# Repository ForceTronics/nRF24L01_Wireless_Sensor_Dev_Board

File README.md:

# nRF24L01_Wireless_Sensor_Dev_Board
This repository is for Arduino code that goes to an open source Wireless Sensor Development Board that is being developed on the ForceTronics YouTube channel. Please note that this code is still currently in early draft form. The Wireless Sensor Dev Board will feature an ATmega 328p MCU and a nRF24L01+ Transceiver Module. The 328p will be programmed using the Arduino IDE (Pro Mini 3.3V 8MHz bootloader). In the future this wireless sensor dev board will be available for sale at www.forcetronics.com

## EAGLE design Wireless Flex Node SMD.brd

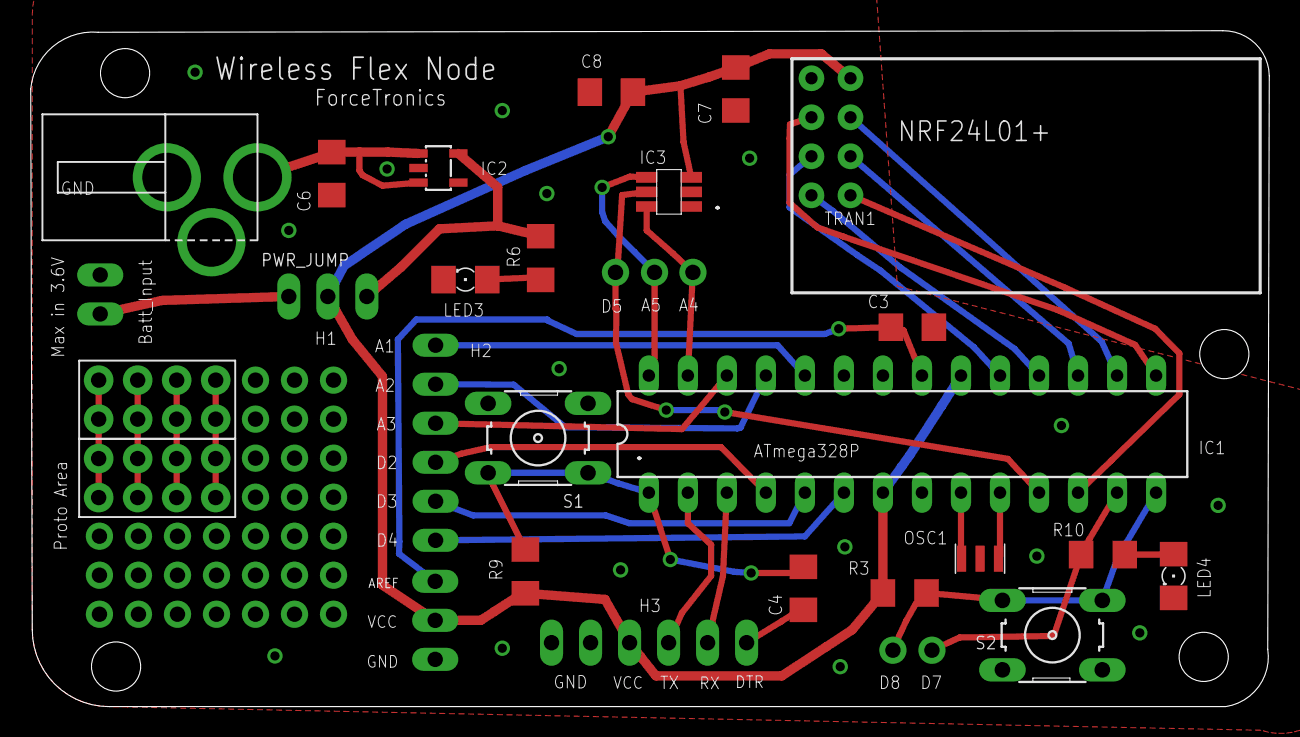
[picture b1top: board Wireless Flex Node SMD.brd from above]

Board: 2 copper layers, 80.6 x 44.0 mm, 31 parts (0 on the bottom side), 35 nets.

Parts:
A4, A5: 1PINHEADER_S
BATT_INPUT: 2PINHEADER
C3, C4, C8: 0.1uF; C1206
C6, C7: 10uF; C1206
D5, D7, D8: 1PINHEADER_S
DGHDFGH: ATMEGA168-PU; DIL28-3
IC2: LP2985; SOT23
LED3, LED4: 1206
N1, N5: 6PINHEADER
N3: 2.1MM_DC_JACK
NRF24L01+: NRF24L01A; NRF24L01
OSC1: CSTCE_RESONATOR
P1, P2: 2X4_HEADER
PWR_JUMP: 3PINHEADER
R3: 100k; R1206
R6, R10: 220; R1206
R9: 10k; R1206
S1, S2: B3F-10XX
U$2: 3PINHEADER
U$8: STTS751; STTS751-SOT23-6L

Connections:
A5: D5.P$1, DGHDFGH.11, U$8.5
GND: BATT_INPUT.P0, C3.2, C6.2, C7.2, C8.2, DGHDFGH.8, DGHDFGH.22, IC2.2, LED3.C, LED4.C, N1.P4, N1.P5, N3.GND1, N3.GND2, NRF24L01+.P1, OSC1.2, S1.3, S1.4, S2.3, S2.4, U$2.N0, U$8.1, U$8.2
unnamed: DGHDFGH.10, OSC1.1
unnamed: DGHDFGH.18, NRF24L01+.P7
unnamed: DGHDFGH.19, NRF24L01+.P5
unnamed: DGHDFGH.17, NRF24L01+.P6
unnamed: DGHDFGH.16, NRF24L01+.P4
unnamed: DGHDFGH.15, NRF24L01+.P3
unnamed: D7.P$1, DGHDFGH.13, R10.2
unnamed: C4.2, N1.P0
unnamed: DGHDFGH.9, OSC1.3
unnamed: C4.1, DGHDFGH.1, R9.1, S1.1, S1.2
unnamed: D8.P$1, DGHDFGH.14, R3.1, S2.1, S2.2
unnamed: LED4.A, R10.1
unnamed: DGHDFGH.3, N1.P1
unnamed: DGHDFGH.2, N1.P2
unnamed: C3.1, DGHDFGH.21, U$2.N2
unnamed: DGHDFGH.12, NRF24L01+.P8
unnamed: DGHDFGH.6, N5.P5
unnamed: DGHDFGH.5, N5.P4
unnamed: A5.P$1, DGHDFGH.28, U$8.4
unnamed: A4.P$1, DGHDFGH.27, U$8.6
unnamed: C6.1, IC2.1, IC2.3, N3.VIN
unnamed: IC2.5, PWR_JUMP.N2, R6.2
unnamed: BATT_INPUT.P1, PWR_JUMP.N0
unnamed: LED3.A, R6.1
unnamed: DGHDFGH.4, N5.P3
unnamed: DGHDFGH.26, N5.P2
unnamed: DGHDFGH.25, N5.P1
unnamed: DGHDFGH.24, N5.P0
unnamed: P1.P1, P1.P5, P2.P1, P2.P5
unnamed: P1.P2, P1.P6, P2.P2, P2.P6
unnamed: P1.P3, P1.P7, P2.P3, P2.P7
unnamed: P1.P4, P1.P8, P2.P4, P2.P8
VCC: C7.1, C8.1, DGHDFGH.7, DGHDFGH.20, N1.P3, NRF24L01+.P2, PWR_JUMP.N1, R3.2, R9.2, U$2.N1, U$8.3

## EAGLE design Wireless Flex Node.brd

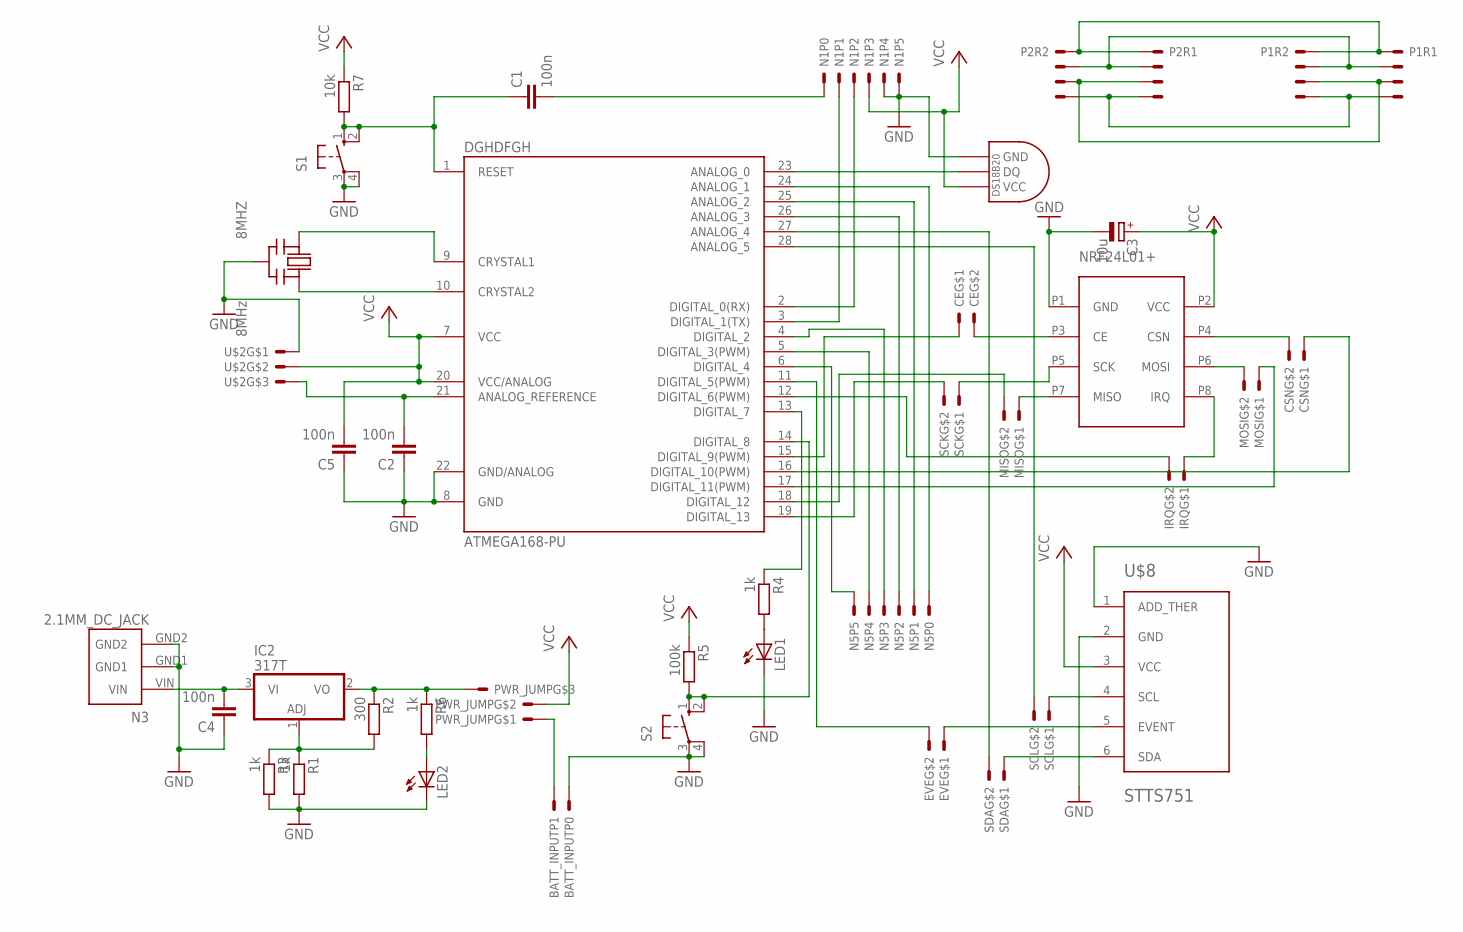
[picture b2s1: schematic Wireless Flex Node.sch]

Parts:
8MHZ: 8MHz; CERM_OSC
BATT_INPUT: 2PINHEADER
C1, C2, C4, C5: 100n; C050-030X075
C3: 10u; E2,5-6
CE: 2PINHEADER_S
CSN: 2PINHEADER_S
DGHDFGH: ATMEGA168-PU; DIL28-3
EVE: 2PINHEADER_S
IC2: 317T; TO220H
IRQ: 2PINHEADER_S
LED1, LED2: LED3MM
MISO: 2PINHEADER_S
MOSI: 2PINHEADER_S
N1, N5: 6PINHEADER
N3: 2.1MM_DC_JACK
NRF24L01+: NRF24L01A; NRF24L01
P1, P2: 2X4_HEADER
PWR_JUMP: 3PINHEADER
R1, R3, R4, R6: 1k; 0207/10
R2: 300; 0207/10
R5: 100k; 0207/10
R7: 10k; 0207/10
S1, S2: 10-XX; B3F-10XX
SCK: 2PINHEADER_S
SCL: 2PINHEADER_S
SDA: 2PINHEADER_S
U$2: 3PINHEADER
U$8: STTS751; STTS751-SOT23-6L
U$9: DS1820TO92; DS1820

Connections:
GND: 8MHZ.P$2 (GND), BATT_INPUT.P0, C2.1, C3.-, C4.1, C5.1, DGHDFGH.8 (GND), DGHDFGH.22 (GND/ANALOG), LED1.K (C), LED2.K (C), N1.P4, N1.P5, N3.GND1, N3.GND2, NRF24L01+.P1 (GND), R1.2, R3.2, S1.3, S1.4 (P1), S2.3, S2.4 (P1), U$2.N0, U$8.1 (ADD_THER), U$8.2 (GND), U$9.GND
unnamed: MISO.N0, NRF24L01+.P7 (MISO)
unnamed: DGHDFGH.18 (DIGITAL_12), MISO.N1
unnamed: DGHDFGH.19 (DIGITAL_13), SCK.N1
unnamed: NRF24L01+.P5 (SCK), SCK.N0
unnamed: MOSI.N1, NRF24L01+.P6 (MOSI)
unnamed: DGHDFGH.17 (DIGITAL_11(PWM)), MOSI.N0
unnamed: CE.N1, NRF24L01+.P3 (CE)
unnamed: CSN.N0, DGHDFGH.16 (DIGITAL_10(PWM))
unnamed: CSN.N1, NRF24L01+.P4 (CSN)
unnamed: CE.N0, DGHDFGH.15 (DIGITAL_9(PWM))
unnamed: DGHDFGH.13 (DIGITAL_7), R4.1
unnamed: C1.2, N1.P0
unnamed: 8MHZ.P$1 (IN), DGHDFGH.9 (CRYSTAL1)
unnamed: 8MHZ.P$3 (OUT), DGHDFGH.10 (CRYSTAL2)
unnamed: C1.1, DGHDFGH.1 (RESET), R7.2, S1.1 (S), S1.2 (S1)
unnamed: DGHDFGH.14 (DIGITAL_8), R5.2, S2.1 (S), S2.2 (S1)
unnamed: LED1.A, R4.2
unnamed: IRQ.N0, NRF24L01+.P8 (IRQ)
unnamed: DGHDFGH.3 (DIGITAL_1(TX)), N1.P1
unnamed: DGHDFGH.2 (DIGITAL_0(RX)), N1.P2
unnamed: C2.2, DGHDFGH.21 (ANALOG_REFERENCE), U$2.N2
unnamed: DGHDFGH.12 (DIGITAL_6(PWM)), IRQ.N1
unnamed: DGHDFGH.6 (DIGITAL_4), N5.P5
unnamed 26: DGHDFGH.23 (ANALOG_0), U$9.DQ; also elsewhere on the board
unnamed: DGHDFGH.5 (DIGITAL_3(PWM)), N5.P4
unnamed: SCL.N0, U$8.4 (SCL)
unnamed: DGHDFGH.28 (ANALOG_5), SCL.N1
unnamed: SDA.N0, U$8.6 (SDA)
unnamed: DGHDFGH.27 (ANALOG_4), SDA.N1
unnamed: EVE.N0, U$8.5 (EVENT)
unnamed: DGHDFGH.11 (DIGITAL_5(PWM)), EVE.N1
unnamed 34: C4.2, IC2.3 (VI), N3.VIN; also elsewhere on the board
unnamed 35: IC2.1 (ADJ), R1.1, R2.2, R3.1; also elsewhere on the board
unnamed 36: IC2.2 (VO), PWR_JUMP.N2, R2.1, R6.1; also elsewhere on the board
unnamed: BATT_INPUT.P1, PWR_JUMP.N0
unnamed: LED2.A, R6.2
unnamed: DGHDFGH.4 (DIGITAL_2), N5.P3
unnamed: DGHDFGH.26 (ANALOG_3), N5.P2
unnamed: DGHDFGH.25 (ANALOG_2), N5.P1
unnamed: DGHDFGH.24 (ANALOG_1), N5.P0
unnamed: P1.P1 (S), P1.P5 (S), P2.P1 (S), P2.P5 (S)
unnamed: P1.P2 (S1), P1.P6 (S1), P2.P2 (S1), P2.P6 (S1)
unnamed: P1.P3 (S2), P1.P7 (S2), P2.P3 (S2), P2.P7 (S2)
unnamed: P1.P4 (S3), P1.P8 (S3), P2.P4 (S3), P2.P8 (S3)
VCC: C3.+, C5.2, DGHDFGH.7 (VCC), DGHDFGH.20 (VCC/ANALOG), N1.P3, NRF24L01+.P2 (VCC), PWR_JUMP.N1, R5.1, R7.1, U$2.N1, U$8.3 (VCC), U$9.VDD (VCC); also elsewhere on the board

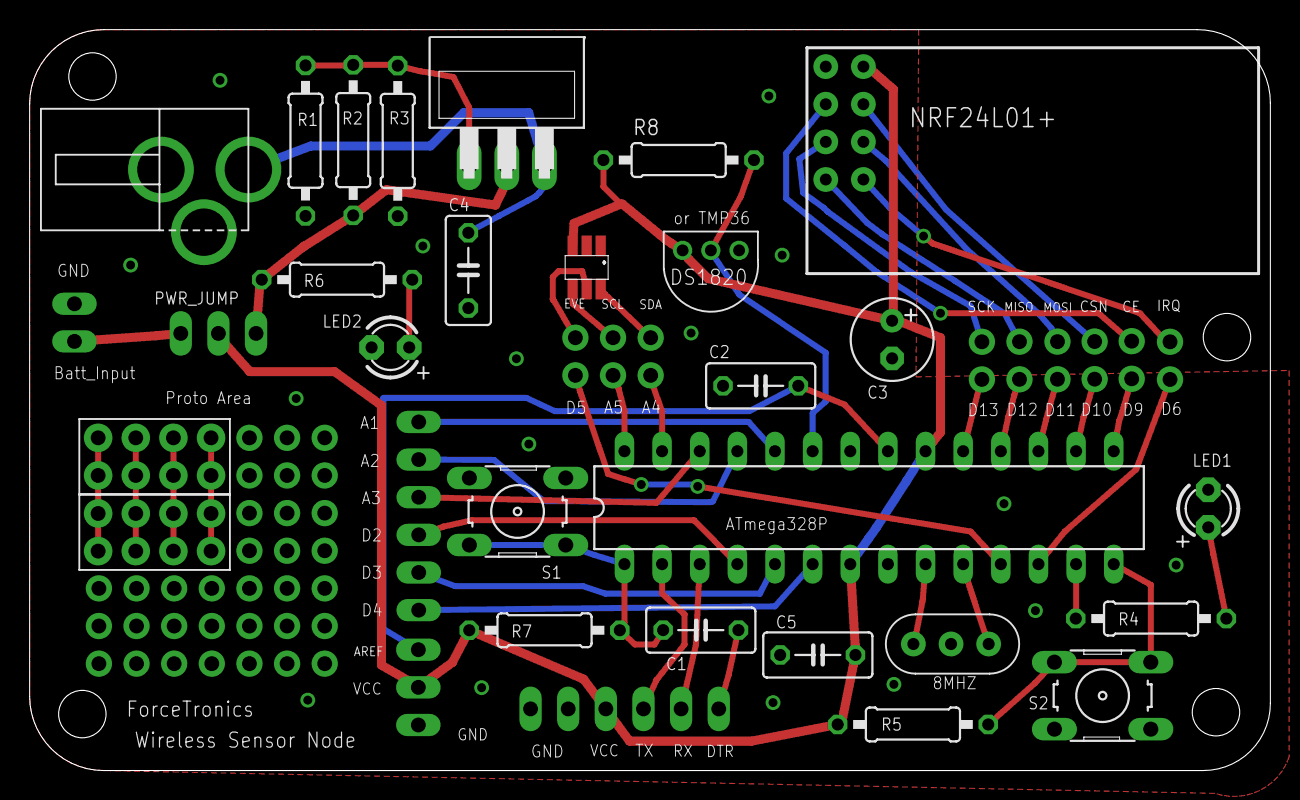
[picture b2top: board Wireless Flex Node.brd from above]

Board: 2 copper layers, 83.7 x 50.0 mm, 40 parts (0 on the bottom side), 46 nets.

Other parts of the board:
IC1: 317T; TO220H
R8: 4.7k; 0207/10

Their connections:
unnamed 26: R8.2; also elsewhere on the board
unnamed 34: IC1.3; also elsewhere on the board
unnamed 35: IC1.1; also elsewhere on the board
unnamed 36: IC1.2; also elsewhere on the board
VCC: R8.1; also elsewhere on the board

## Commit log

2016-01-06 Create nRF24_Network_Router_End_Device.ino
    For a description of this code and project go to the ForceTronics YouTube Channel: https://www.youtube.com/channel/UCNd_fNspAczm8UoE2ay7K1Q
2016-01-06 Create Wireless_Sensor_Network_Coordinator.ino
    This code is just meant to serve as a simple coordinator in an RF24Network to demonstrate the router and end device code. For more information on this project go to the ForceTronics YouTube Channel h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
2016-01-21 Create Wireless Flex Node.sch
    This is the schematic file for Eagle PCB layout software
2016-01-21 Create Wireless Flex Node.brd
    Board file for Eagle PCB layout software
2016-01-21 Update nRF24_Network_Router_End_Device.ino
    Wireless sensor node Arduino code.
2016-01-21 Create ForceTronics.lbr
    This library file for the Eagle PCB software should be added to the Eagle lbr file folder when using the wireless sensor node Eagle files since parts from this library file are used in the wireless s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
2016-03-15 Create nRF24_Network_Router_End_Device_STTS751.ino
    This version of the code was made for the STTS751 Temperature sensor. Please note that this code will only work with the maniacbug R24 and RF24Network libraries on GitHub.
2016-03-15 Create nRF24_Network_Router_End_Device_DS18S20.ino
    This version of the code was made for the DS18S20 Temperature sensor, which requires that you have the DallasTemperature.h and OneWire.h libraries. Please note that this code will only work with the 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
2016-03-15 Create nRF24_Network_Router_End_Device_TMP36.ino
    This version of the code was made for the TMP36 Temperature sensor. Please note that this code will only work with the maniacbug R24 and RF24Network libraries on GitHub.
2016-06-17 Create WSNode.cpp
    One of two library files for the Wireless Flex Node software wrapper
2016-06-17 Create WSNode.h
    One of two library files for Arduino based wireless flex node board
2016-06-17 Create nRF24_Wireless_Node.ino
    Arduino sketch for wireless flex node board found at forcetronics.com. The sketch uses WSNode library files found here also.
2016-06-17 Update Wireless_Sensor_Network_Coordinator.ino
    This Arduino sketch is meant to provide example Coordinator code for the wireless flex node design.
2016-06-17 nRF24_Wireless_Node description
    This Arduino sketch is for the Wireless Flex Node board by ForceTronics.com. It creates a router or end device for a network of nRF24L01 transceivers using the RF24Network library TMRh20 version whic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
2016-06-17 nRF24_Network_Router_End_Device_NoLib
    This Arduino sketch is for the Wireless Flex Node board by ForceTronics.com. It creates a router or end device for a network of nRF24L01 transceivers using the RF24Network library TMRh20 version whic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
2016-06-18 Description Wireless Flex Node SMD.sch
    Schematic file for Eagle PCB software of Wireless Flex Node design
2016-06-18 Description Wireless Flex Node SMD.brd
    Eagle board file for the forcetronics Wireless Flex Node design.
